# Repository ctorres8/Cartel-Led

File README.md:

# Cartel-Led
 Proyecto para la materia Técnicas Digitales II. Se trata de un cartel programable que pueda ser utilizado para satisfacer las necesidades básicas de un usuario, como
conocer la fecha y hora actual, la temperatura en el ambiente, o para enunciar a través de él algún mensaje para alertar o informar alguna novedad.

Va a utilizar:
* **Bluetooh:** Para enviar y recibir mensajes
* **SD:** Para recibir mensajes
* **Sensores de luz y temperatura:** Para sensor la luz del ambiente y medir temperatura.
* **RTC:** Reloj en tiempo real para tener la hora y fecha actual.
* **4 Matrices LED 8X8:** Para observar la fecha,hora, temperatura y mensajes recibidos
* **Teclado:** Para una comunicación manual con el cartel.

*El proyecto se encuentra explicado de manera más informativo en el informe (Documentación->informe)* 

# Organización del repositorio:

* **Anteproyecto:** Idea fuerza y presentación del anteproyecto.
* **Datasheets:** Hojas de datos de los componentes utilizados en el proyecto
* **Dristribución de pines:** Distribución de pines y componentes para cada integrante del grupo
* **Documentación:** Informe y manual técnico y de usuario del proyecto
* **Proyecto_Nucleo_Kicad:** Esquemáticos y diseños de PCB
* **Proyecto_STM32:** Código en C con las librerías utilzadas en el proyecto

# Videos de funcionamiento
En el siguiente link se pueden ver algunos videos cortos sobre el funcionamiento del cartel.

Link: https://drive.google.com/drive/folders/1nYiywO-ZSkL0tqdU_d7GqGv7mtErooJ5?usp=share_link

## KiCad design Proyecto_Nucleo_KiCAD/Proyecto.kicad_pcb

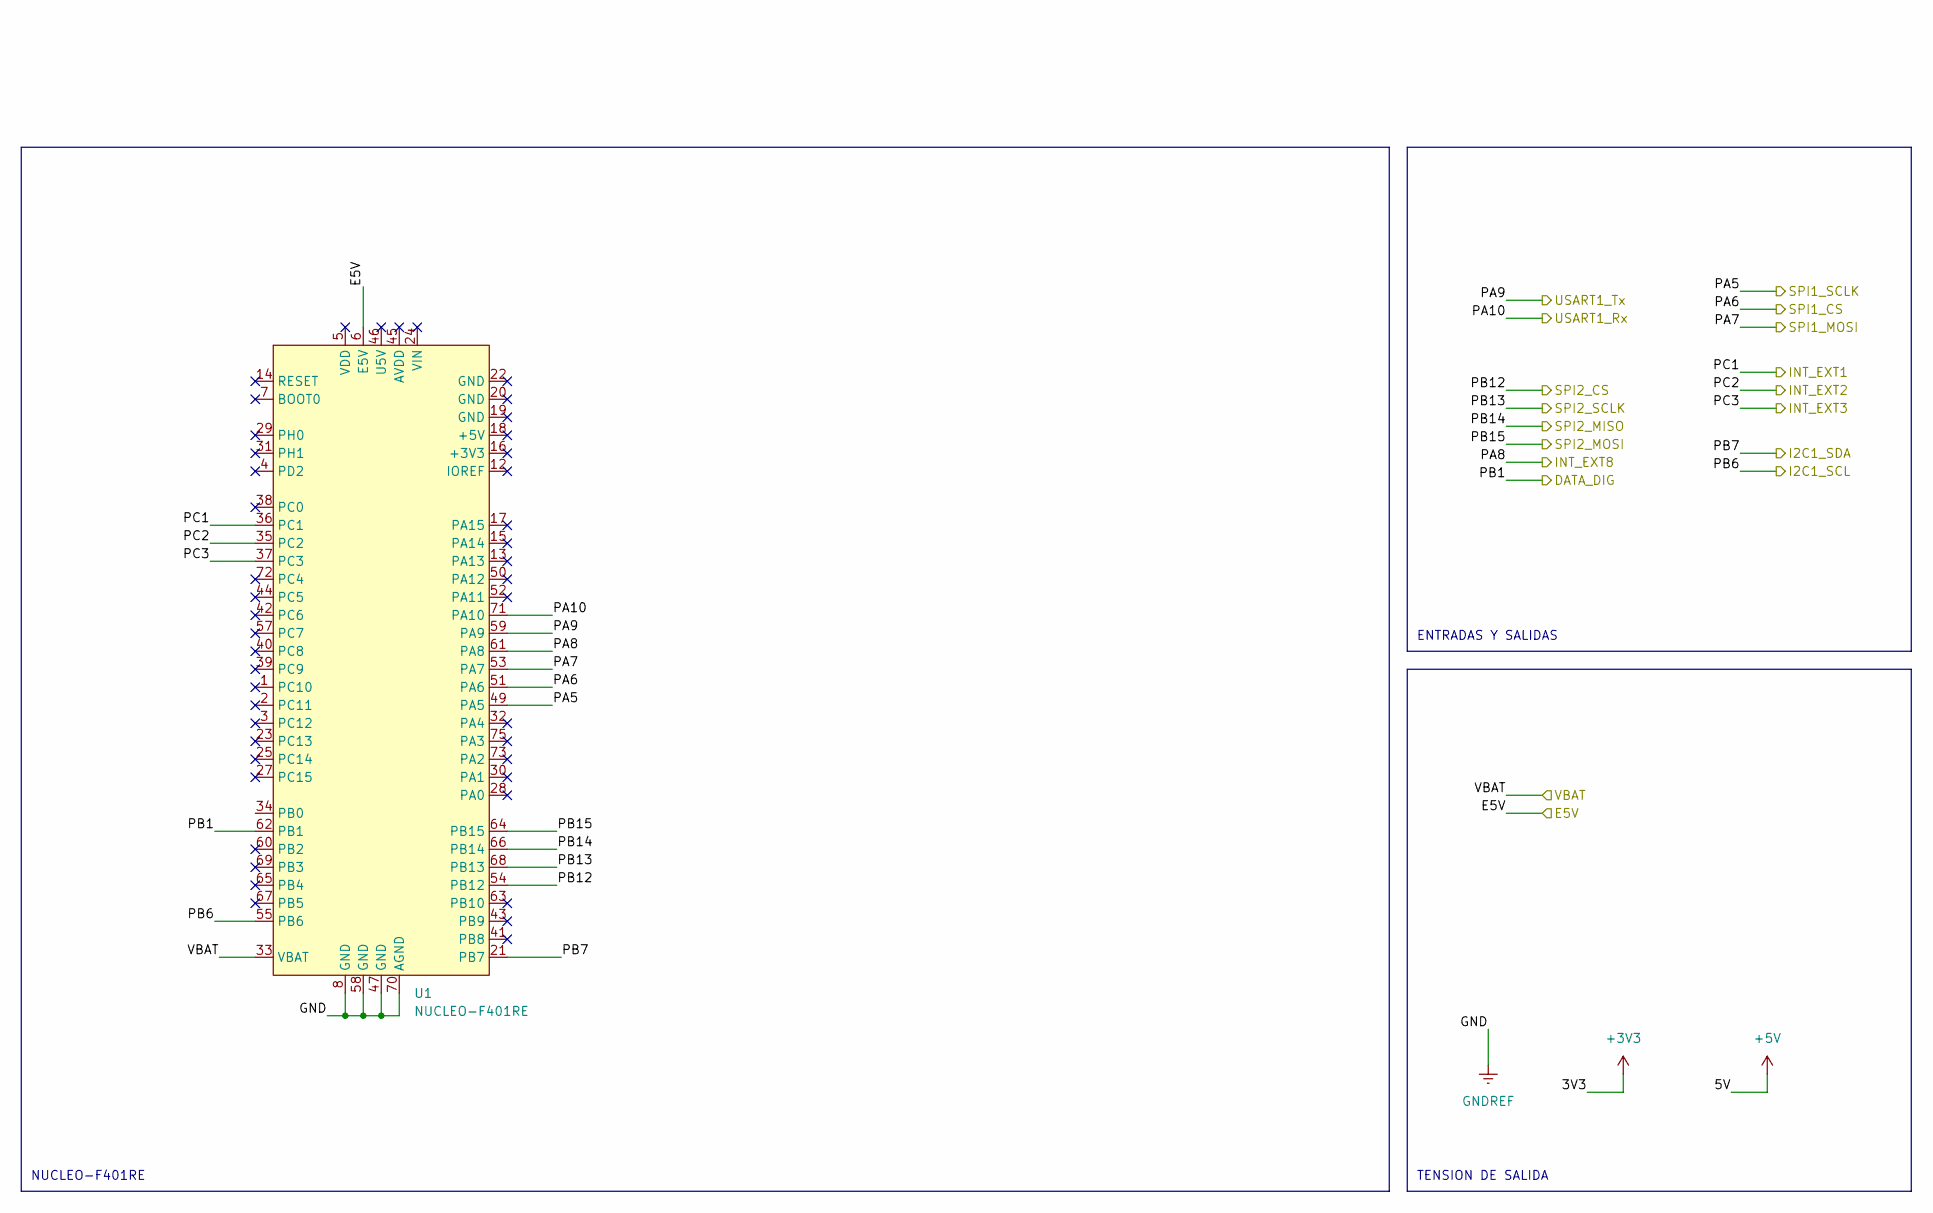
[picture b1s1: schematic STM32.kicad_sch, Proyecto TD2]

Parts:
U1: NUCLEO-F401RE; ST_NUCLEO-F401RE

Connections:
+5V: U1.6 (E5V); also elsewhere on the board
/EntradasSalidas/CS: U1.54 (PB12); also elsewhere on the board
/EntradasSalidas/MISO: U1.66 (PB14); also elsewhere on the board
/EntradasSalidas/MOSI: U1.64 (PB15); also elsewhere on the board
/EntradasSalidas/SCLK: U1.68 (PB13); also elsewhere on the board
/STM32/PA5: U1.49 (PA5); also elsewhere on the board
/STM32/PA6: U1.51 (PA6); also elsewhere on the board
/STM32/PA7: U1.53 (PA7); also elsewhere on the board
/STM32/PA8: U1.61 (PA8); also elsewhere on the board
/STM32/PA9: U1.59 (PA9); also elsewhere on the board
/STM32/PA10: U1.71 (PA10); also elsewhere on the board
/STM32/PB1: U1.62 (PB1); also elsewhere on the board
/STM32/PB6: U1.55 (PB6); also elsewhere on the board
/STM32/PB7: U1.21 (PB7); also elsewhere on the board
/STM32/PC1: U1.36 (PC1); also elsewhere on the board
/STM32/PC2: U1.35 (PC2); also elsewhere on the board
/STM32/PC3: U1.37 (PC3); also elsewhere on the board
/STM32/VBAT: U1.33 (VBAT); also elsewhere on the board
GNDREF: U1.8 (GND), U1.47 (GND), U1.58 (GND), U1.70 (AGND); also elsewhere on the board

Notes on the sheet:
ENTRADAS Y SALIDAS
NUCLEO-F401RE
TENSION DE SALIDA

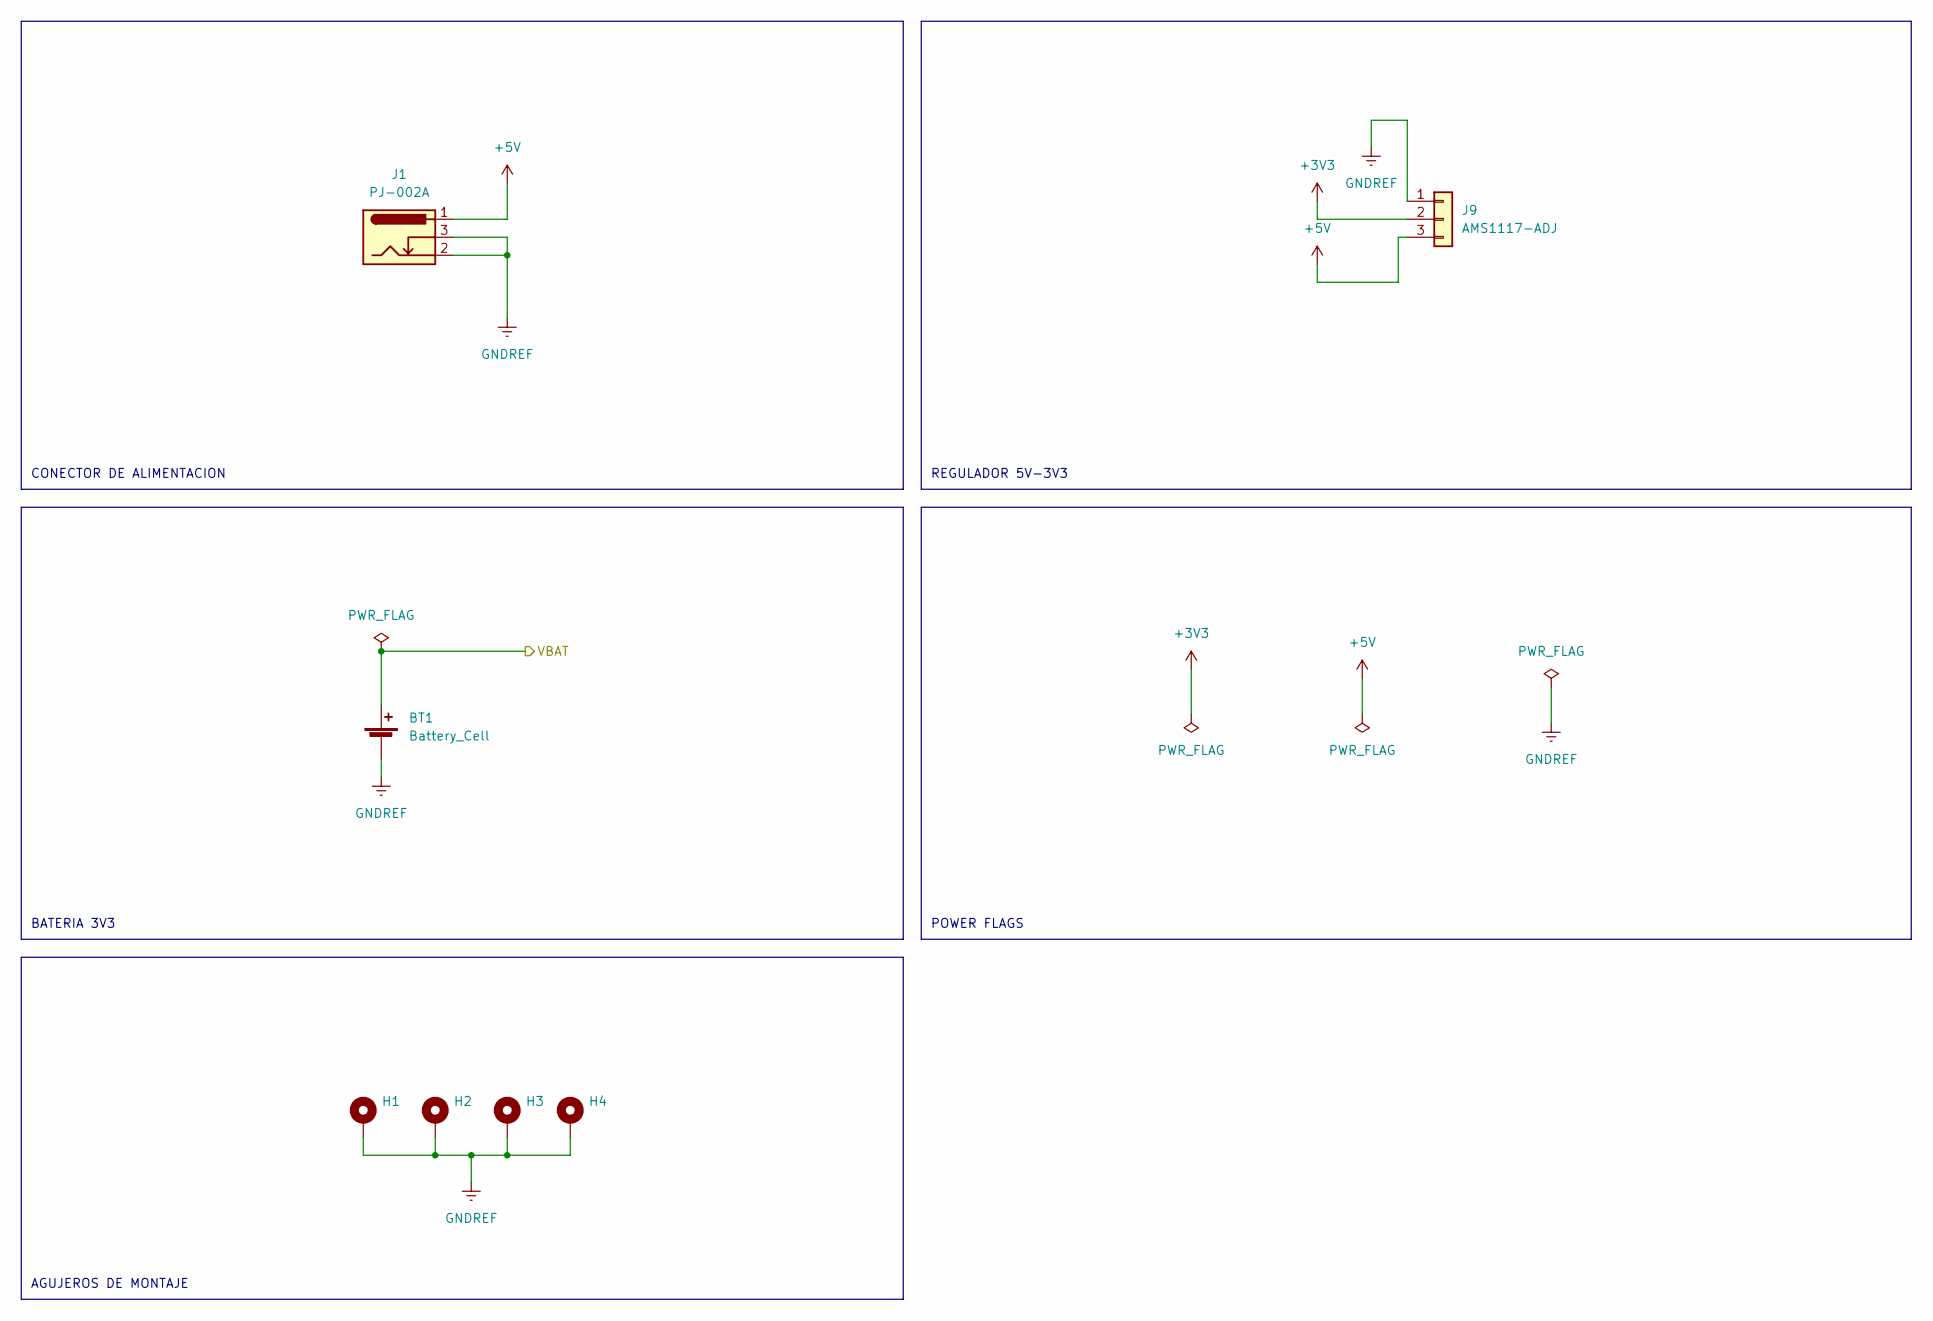
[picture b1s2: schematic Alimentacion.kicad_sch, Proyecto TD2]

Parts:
BT1: Battery_Cell; BatteryHolder_Keystone_103_1x20mm
H1, H2, H3, H4: MountingHole_Pad; MountingHole_2.5mm_Pad
J1: PJ-002A
J9: AMS1117-ADJ

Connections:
+3V3: J9.2; also elsewhere on the board
+5V: J1.1, J9.3; also elsewhere on the board
/STM32/VBAT: BT1.1 (+); also elsewhere on the board
GNDREF: BT1.2 (-), H1.1, H2.1, H3.1, H4.1, J1.2, J1.3, J9.1; also elsewhere on the board

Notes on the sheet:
CONECTOR DE ALIMENTACION
BATERIA 3V3
AGUJEROS DE MONTAJE
REGULADOR 5V-3V3
POWER FLAGS

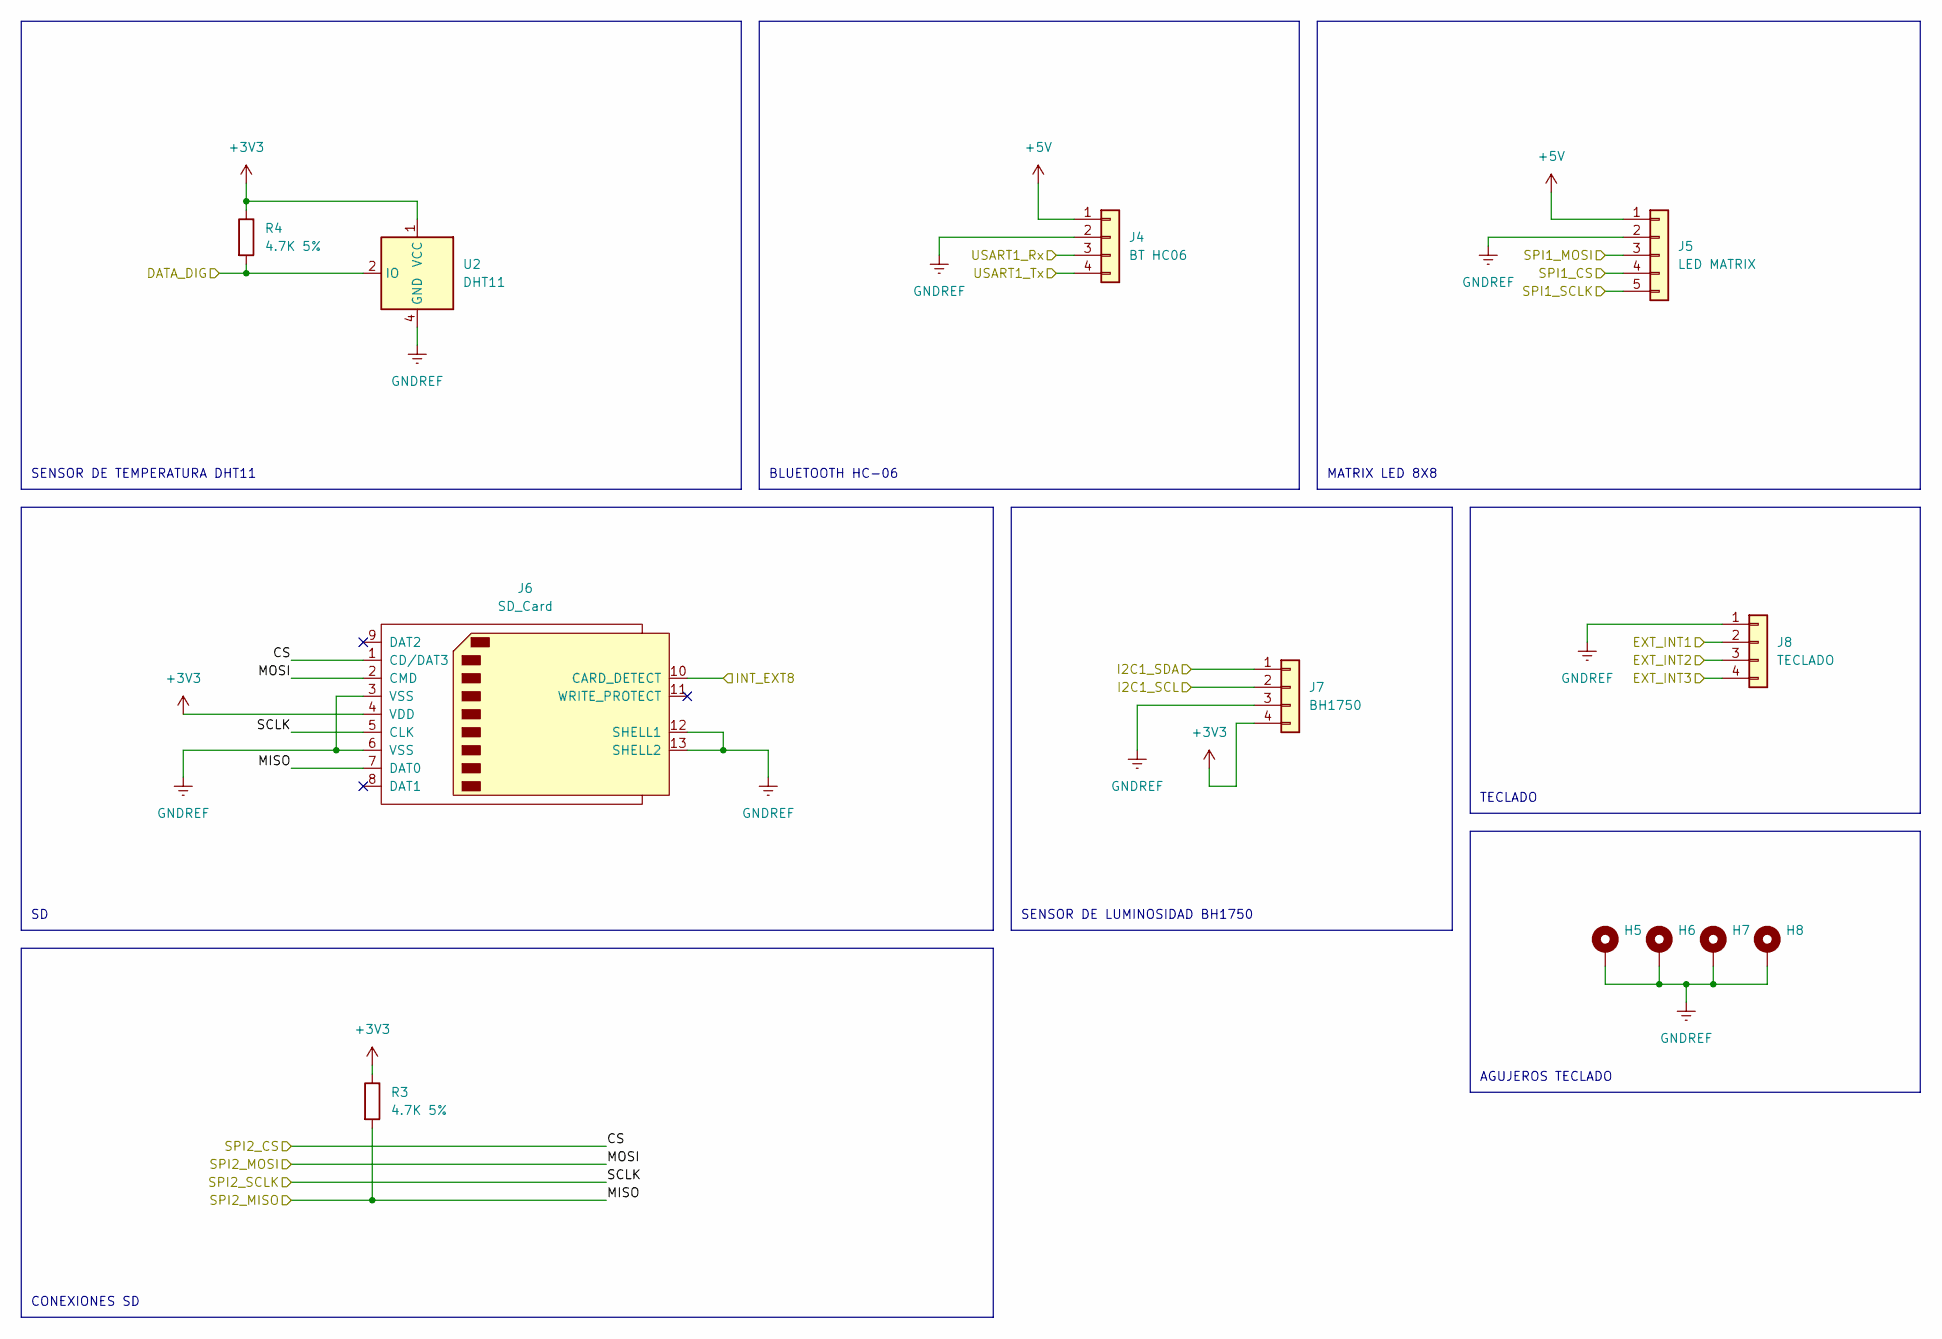
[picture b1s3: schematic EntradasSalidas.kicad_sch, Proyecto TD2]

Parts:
H5, H6, H7, H8: MountingHole_Pad; MountingHole_2.5mm_Pad
J4: BT HC06; HC06
J5: LED MATRIX; PinSocket_1x05_P2.54mm_Vertical
J6: SD_Card; footprint_SD_GSD09002SEU
J7: BH1750; PinSocket_1x04_P2.54mm_Vertical
J8: TECLADO; PinSocket_1x04_P2.54mm_Vertical
R3, R4: 4.7K 5%; R_Axial_DIN0207_L6.3mm_D2.5mm_P15.24mm_Horizontal
U2: DHT11; Aosong_DHT11_5.5x12.0_P2.54mm

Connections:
+3V3: J6.4 (VDD), J7.4, R3.1, R4.1, U2.1 (VCC); also elsewhere on the board
+5V: J4.1, J5.1; also elsewhere on the board
/EntradasSalidas/CS: J6.1 (CD/DAT3); also elsewhere on the board
/EntradasSalidas/MISO: J6.7 (DAT0), R3.2; also elsewhere on the board
/EntradasSalidas/MOSI: J6.2 (CMD); also elsewhere on the board
/EntradasSalidas/SCLK: J6.5 (CLK); also elsewhere on the board
/STM32/PA5: J5.5; also elsewhere on the board
/STM32/PA6: J5.4; also elsewhere on the board
/STM32/PA7: J5.3; also elsewhere on the board
/STM32/PA8: J6.10 (CARD_DETECT); also elsewhere on the board
/STM32/PA9: J4.4; also elsewhere on the board
/STM32/PA10: J4.3; also elsewhere on the board
/STM32/PB1: R4.2, U2.2 (IO); also elsewhere on the board
/STM32/PB6: J7.2; also elsewhere on the board
/STM32/PB7: J7.1; also elsewhere on the board
/STM32/PC1: J8.2; also elsewhere on the board
/STM32/PC2: J8.3; also elsewhere on the board
/STM32/PC3: J8.4; also elsewhere on the board
GNDREF: H5.1, H6.1, H7.1, H8.1, J4.2, J5.2, J6.3 (VSS), J6.6 (VSS), J6.12 (SHELL1), J6.13 (SHELL2), J7.3, J8.1, U2.4 (GND); also elsewhere on the board

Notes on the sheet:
BLUETOOTH HC-06
SENSOR DE TEMPERATURA DHT11
SENSOR DE LUMINOSIDAD BH1750
TECLADO
AGUJEROS TECLADO
CONEXIONES SD
MATRIX LED 8X8

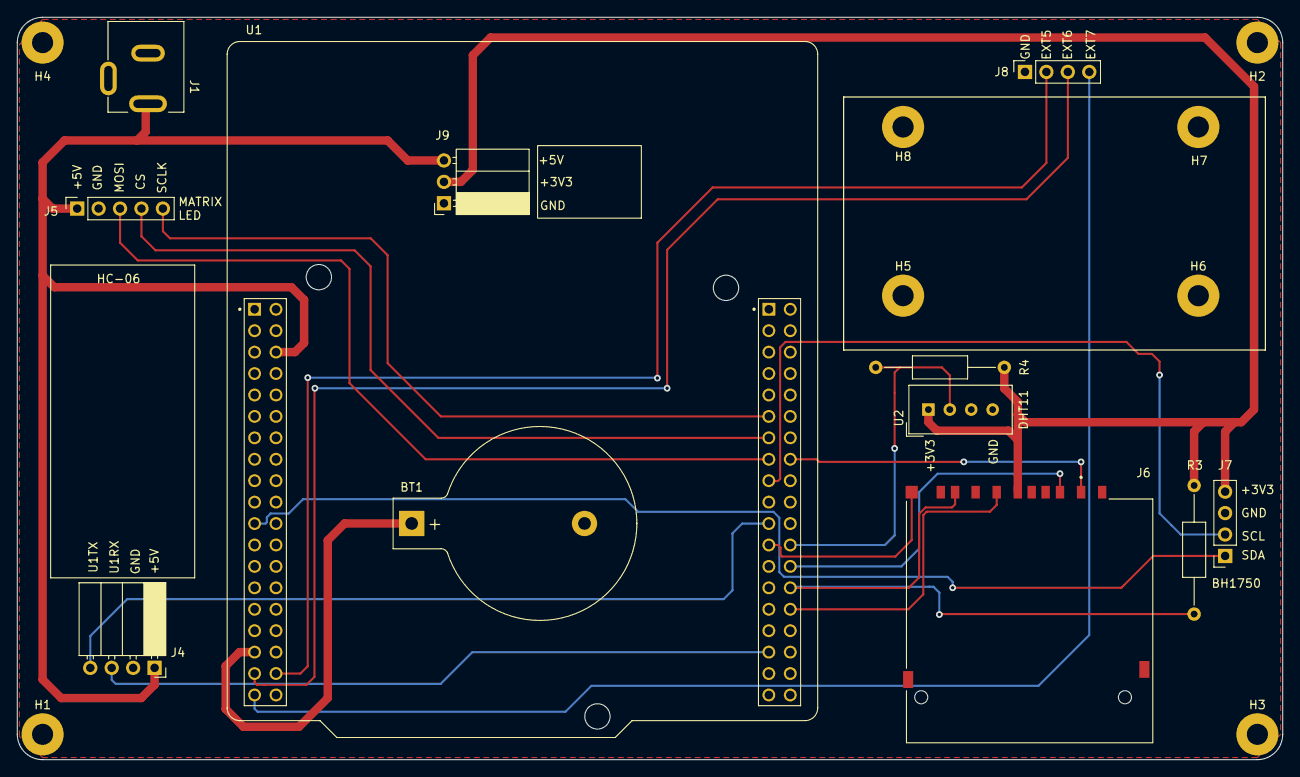
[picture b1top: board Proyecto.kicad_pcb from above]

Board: 2 copper layers, 150.0 x 88.0 mm, 20 parts (0 on the bottom side), 20 nets.

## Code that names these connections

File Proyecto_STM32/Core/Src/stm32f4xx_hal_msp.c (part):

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
    __HAL_RCC_GPIOB_CLK_ENABLE();
    /**I2C1 GPIO Configuration
    PB6     ------> I2C1_SCL
    PB7     ------> I2C1_SDA
    */
    GPIO_InitStruct.Pin = GPIO_PIN_6|GPIO_PIN_7;
    GPIO_InitStruct.Mode = GPIO_MODE_AF_OD;
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    __HAL_RCC_I2C1_CLK_DISABLE();

    /**I2C1 GPIO Configuration
    PB6     ------> I2C1_SCL
    PB7     ------> I2C1_SDA
    */
    HAL_GPIO_DeInit(GPIOB, GPIO_PIN_6);

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
    __HAL_RCC_GPIOA_CLK_ENABLE();
    /**SPI1 GPIO Configuration
    PA5     ------> SPI1_SCK
    PA7     ------> SPI1_MOSI
    */
    GPIO_InitStruct.Pin = GPIO_PIN_5|GPIO_PIN_7;
    GPIO_InitStruct.Mode = GPIO_MODE_AF_PP;
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
    __HAL_RCC_GPIOB_CLK_ENABLE();
    /**SPI2 GPIO Configuration
    PB13     ------> SPI2_SCK
    PB14     ------> SPI2_MISO
    PB15     ------> SPI2_MOSI
    */
    GPIO_InitStruct.Pin = GPIO_PIN_13|GPIO_PIN_14|GPIO_PIN_15;
    GPIO_InitStruct.Mode = GPIO_MODE_AF_PP;
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    __HAL_RCC_SPI1_CLK_DISABLE();

    /**SPI1 GPIO Configuration
    PA5     ------> SPI1_SCK
    PA7     ------> SPI1_MOSI
    */
    HAL_GPIO_DeInit(GPIOA, GPIO_PIN_5|GPIO_PIN_7);

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    __HAL_RCC_SPI2_CLK_DISABLE();

    /**SPI2 GPIO Configuration
    PB13     ------> SPI2_SCK
    PB14     ------> SPI2_MISO
    PB15     ------> SPI2_MOSI
    */
    HAL_GPIO_DeInit(GPIOB, GPIO_PIN_13|GPIO_PIN_14|GPIO_PIN_15);

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
    __HAL_RCC_GPIOA_CLK_ENABLE();
    /**USART1 GPIO Configuration
    PA9     ------> USART1_TX
    PA10     ------> USART1_RX
    */
    GPIO_InitStruct.Pin = GPIO_PIN_9|GPIO_PIN_10;
    GPIO_InitStruct.Mode = GPIO_MODE_AF_PP;
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    __HAL_RCC_USART1_CLK_DISABLE();

    /**USART1 GPIO Configuration
    PA9     ------> USART1_TX
    PA10     ------> USART1_RX
    */
    HAL_GPIO_DeInit(GPIOA, GPIO_PIN_9|GPIO_PIN_10);

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
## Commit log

2022-12-19 Primera Entrega
    Primera Entrega.

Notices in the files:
Proyecto_STM32/Core/Src/stm32f4xx_hal_msp.c:
Copyright (c) 2022 STMicroelectronics.
All rights reserved.
This software is licensed under terms that can be found in the LICENSE file
